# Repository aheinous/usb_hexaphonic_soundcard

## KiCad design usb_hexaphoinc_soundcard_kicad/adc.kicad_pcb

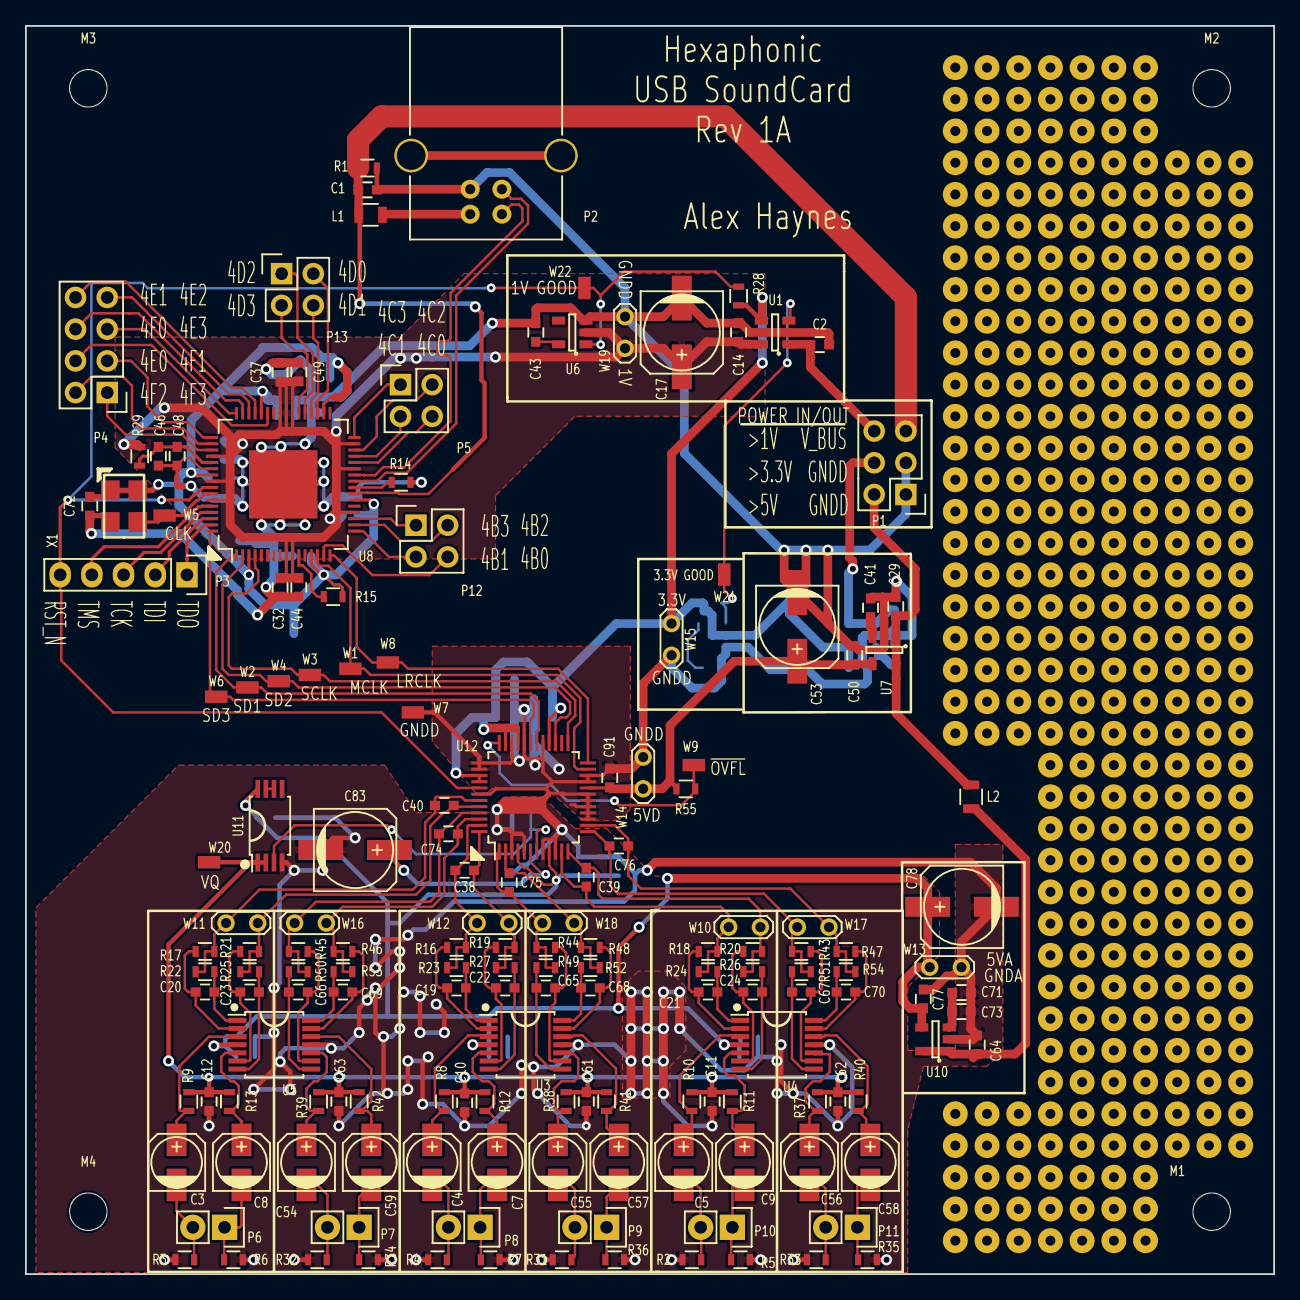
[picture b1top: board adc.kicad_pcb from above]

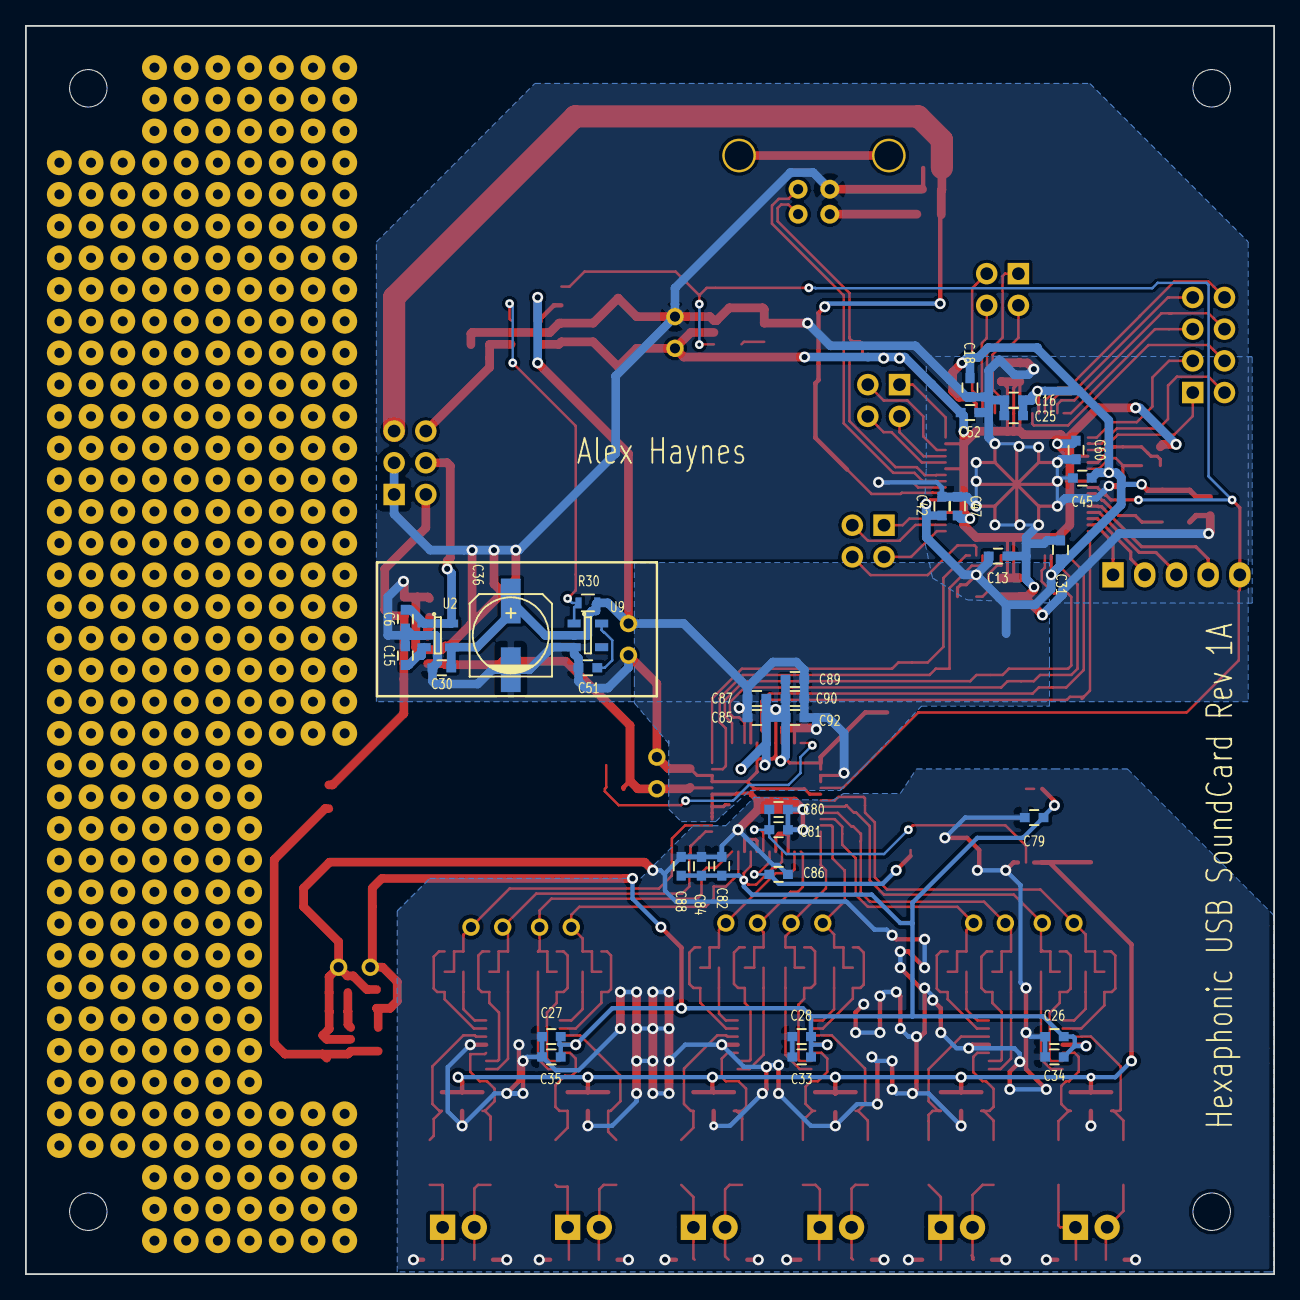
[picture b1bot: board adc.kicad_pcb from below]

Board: 2 copper layers, 100.0 x 100.0 mm, 203 parts (36 on the bottom side), 121 nets.

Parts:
C1, C14: 2.2uF; C_0603
C2, C13, C16, C32, C37, C46, C80, C88, C89: 1uF; C_0603
C3, C4, C5, C7, C8, C9, C54, C55, C56, C57, C58, C59: 10uF; c_elec_4x4.5
C6, C10, C11, C12, C18, C25, C26, C27, C28, C29, C31, C42, C44, C45, C47, C48, C49, C52, C60, C61, C62, C63, C64, C71, C72, C79, C81, C84, C86, C87, C90, C91: 100nF; C_0603
C15, C33, C34, C35, C41, C43, C51, C73, C82, C85, C92: 10nF; C_0603
C17, C36, C53, C78, C83: 220uF; c_elec_6.3x7.7
C19, C20, C21, C22, C23, C24, C65, C66, C67, C68, C69, C70: 470pF; C_0603
C30, C50, C77: 4.7uF; C_0603
C38, C39, C40, C74, C75, C76: 2700pF; C_0603
L1, L2: MPZ2012S102A; R_0805
M1, M2, M3, M4: mounting_hole; MountingHole_3mm
P1: CONN_02X03; Pin_Header_Straight_2x03
P2: USB_B
P3: CONN_01X05; Pin_Header_Straight_1x05
P4: CONN_02X04; Pin_Header_Straight_2x04
P5, P12, P13: CONN_02X02; Pin_Header_Straight_2x02
P6, P7, P8, P9, P10, P11: CONN_01X02; Pin_Header_Straight_1x02
R1, R2, R3, R4, R5, R6, R7, R28, R30, R31, R32, R33, R34, R35, R36, R55: 100k; R_0603
R8, R9, R10, R11, R12, R13, R37, R38, R39, R40, R41, R42: 10k; R_0603
R14: 43.2R 1%; R_0603
R15: 1k; R_0603
R16, R17, R18, R19, R20, R21, R43, R44, R45, R46, R47, R48: 634R; R_0603
R22, R23, R24, R25, R26, R27, R49, R50, R51, R52, R53, R54: 91R; R_0603
R29: 4.7R; R_0603
ST1: star_pt; star_connect_2
ST2: star_pt_2; star_connect_2
U1: NCP4671DSN10T1G; SOT-23-5
U2: NJM2870F33; SOT-23-5
U3, U4, U5: OPA1654; TSSOP-14_4.4x5mm_Pitch0.65mm_better
U6: NCP303; SOT-23-5
U7, U10: NJM2870F05; SOT-23-5
U8: XUF208-128-TQ64; LQFP-64_10x10mm_Pitch0.5mm_center_pad
U9: BD5331G-TR; SOT-23-5
U11: TL072; TSSOP-8_4.4x3mm_Pitch0.65mm_better
U12: CS5366; LQFP-48_7x7mm_Pitch0.5mm_better
W1, W2, W3, W4, W5, W6, W7, W8, W9, W20, W21, W22: TEST_1P; test_point_harwin_S2761-46R
W10, W11, W12, W13, W14, W15, W16, W17, W18, W19: TEST; Test_Point_2Pads
X1: 24MHz; SG5032_crystal_oscillator

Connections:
+3V3: C13.1, C16.1, C18.1, C25.1, C30.1, C31.1, C36.1, C42.1, C45.1, C72.1, C85.1, C87.1, C89.1, C90.1, C92.1, R15.2, R28.1, R30.1, U1.4, U2.4, U8.3, U8.13, U8.22, U8.34, U8.44, U8.55, U9.2, U12.28, U12.33, U12.35, U12.39, U12.40, W15.1, X1.1, X1.4
/Buffer_1_2/ADC_A+: C40.1, R21.1, R25.2, U12.44, W11.2
/Buffer_1_2/ADC_A-: C40.2, R17.1, R22.2, U12.43, W11.1
/Buffer_1_2/ADC_B+: C74.1, R46.1, R53.2, U12.46, W16.2
/Buffer_1_2/ADC_B-: C74.2, R45.1, R50.2, U12.45, W16.1
/Buffer_1_2/IN_A+: C8.2, P6.1, R6.2
/Buffer_1_2/IN_A-: C3.2, P6.2, R3.2
/Buffer_1_2/IN_B+: C59.2, P7.1, R34.2
/Buffer_1_2/IN_B-: C54.2, P7.2, R32.2
/Buffer_1_2/VQ: C10.2, C11.2, C12.2, C61.2, C62.2, C63.2, R8.1, R9.1, R10.1, R11.2, R12.2, R13.2, R37.1, R38.1, R39.1, R40.2, R41.2, R42.2, U11.1, U11.2, W20.1
/Buffer_4_3/ADC_A+: C38.1, R19.1, R27.2, U12.48, W12.2
/Buffer_4_3/ADC_A-: C38.2, R16.1, R23.2, U12.47, W12.1
/Buffer_4_3/ADC_B+: C75.1, R48.1, R52.2, U12.2, W18.2
/Buffer_4_3/ADC_B-: C75.2, R44.1, R49.2, U12.1, W18.1
/Buffer_4_3/IN_A+: C7.2, P8.1, R7.2
/Buffer_4_3/IN_A-: C4.2, P8.2, R4.2
/Buffer_4_3/IN_B+: C57.2, P9.1, R36.2
/Buffer_4_3/IN_B-: C55.2, P9.2, R31.2
/Buffer_6_5/ADC_A+: C39.1, R20.1, R26.2, U12.12, W10.2
/Buffer_6_5/ADC_A-: C39.2, R18.1, R24.2, U12.11, W10.1
/Buffer_6_5/ADC_B+: C76.1, R47.1, R54.2, U12.14, W17.2
/Buffer_6_5/ADC_B-: C76.2, R43.1, R51.2, U12.13, W17.1
/Buffer_6_5/IN_A+: C9.2, P10.1, R5.2
/Buffer_6_5/IN_A-: C5.2, P10.2, R2.2
/Buffer_6_5/IN_B+: C58.2, P11.1, R35.2
/Buffer_6_5/IN_B-: C56.2, P11.2, R33.2
/FILT+: C83.1, C86.1, U12.6
/MCU/4B0: P12.4, U8.15
/MCU/4B1: P12.3, U8.17
/MCU/4B2: P12.2, U8.18
/MCU/4B3: P12.1, U8.19
/MCU/4C0: P5.4, U8.28
/MCU/4C1: P5.3, U8.29
/MCU/4C2: P5.2, U8.30
/MCU/4C3: P5.1, U8.32
/MCU/4D0: P13.2, U8.35
/MCU/4D1: P13.4, U8.36
/MCU/4D2: P13.1, U8.37
/MCU/4D3: P13.3, U8.38
/MCU/4E0: P4.4, U8.43
/MCU/4E1: P4.8, U8.45
/MCU/4E2: P4.7, U8.46
/MCU/4E3: P4.5, U8.48
/MCU/4F0: P4.6, U8.47
/MCU/4F1: P4.3, U8.49
/MCU/4F2: P4.2, U8.50
/MCU/4F3: P4.1, U8.51
/MCU/CLK: U8.58, W5.1, X1.3
/MCU/LRCLK: U8.16, U12.24, W8.1
/MCU/MCLK: U8.14, U12.23, W1.1
/MCU/SCLK: U8.4, U12.25, W3.1
/MCU/SD1: U8.1, U12.30, W2.1
/MCU/SD2: U8.2, U12.27, W4.1
/MCU/SD3: U8.64, U12.31, W6.1
/MCU/USB_D+: P2.3, U8.25
/MCU/USB_D-: P2.2, U8.26
/MCU/V_BUS: C1.1, L1.1, P1.5, R1.2, U8.23
/Power/1V_GOOD: P3.5, R28.2, U6.1, U8.57, U12.41, W22.1
/Power/3.3V_GOOD: R30.2, U1.3, U9.1, W21.1
/Power/GT_1V: C2.1, P1.6, U1.1
/Power/GT_5V: C29.1, L2.1, P1.2, U7.1, U7.5
/Power/GT_33V: C6.1, P1.4, U2.1, U2.5
/VQ: C80.1, C81.1, U11.3, U12.7
Earth_Clean: C46.2, C48.2, ST1.2, U8.54
GNDA: C10.1, C11.1, C12.1, C26.1, C27.1, C28.1, C33.1, C34.1, C35.1, C61.1, C62.1, C63.1, C64.2, C71.2, C73.2, C77.2, C78.2, C79.2, C80.2, C81.2, C82.2, C83.2, C84.2, C86.2, C88.2, R2.1, R3.1, R4.1, R5.1, R6.1, R7.1, R31.1, R32.1, R33.1, R34.1, R35.1, R36.1, ST2.1, U3.11, U4.11, U5.11, U10.2, U11.4, U12.3, U12.5, U12.8, U12.10, W13.2
GNDD: C1.2, C2.2, C6.2, C13.2, C14.2, C15.2, C16.2, C17.2, C18.2, C25.2, C29.2, C30.2, C31.2, C32.2, C36.2, C37.2, C41.2, C42.2, C43.2, C44.2, C45.2, C47.2, C49.2, C50.2, C51.2, C52.2, C53.2, C60.2, C72.2, C85.2, C87.2, C89.2, C90.2, C91.2, C92.2, P1.1, P1.3, P2.4, R1.1, R14.2, ST1.1, ST2.2, U1.2, U2.2, U6.3, U7.2, U8.GND, U9.3, U12.15, U12.16, U12.17, U12.18, U12.19, U12.21, U12.22, U12.29, U12.32, U12.34, U12.37, U12.38, U12.42, W7.1, W14.2, W15.2, W19.2, X1.2
unnamed: C3.1, R9.2, U5.3
unnamed: C4.1, R8.2, U3.3
unnamed: C5.1, R10.2, U4.3
unnamed: C7.1, R12.1, U3.5
unnamed: C8.1, R13.1, U5.5
unnamed: C9.1, R11.1, U4.5
unnamed: C15.1, U2.3
unnamed: C19.1, R23.1, U3.1
unnamed: C19.2, R16.2, U3.2
unnamed: C20.1, R22.1, U5.1
unnamed: C20.2, R17.2, U5.2
unnamed: C21.1, R24.1, U4.1
unnamed: C21.2, R18.2, U4.2
unnamed: C22.1, R27.1, U3.7
unnamed: C22.2, R19.2, U3.6
unnamed: C23.1, R25.1, U5.7
unnamed: C23.2, R21.2, U5.6
unnamed: C24.1, R26.1, U4.7
unnamed: C24.2, R20.2, U4.6
unnamed: C41.1, U7.3
unnamed: C43.1, U6.5
unnamed: C46.1, C48.1, R29.2, U8.53
unnamed: C51.1, U9.5
unnamed: C54.1, R39.2, U5.10
unnamed: C55.1, R38.2, U3.10
unnamed: C56.1, R37.2, U4.10
unnamed: C57.1, R41.1, U3.12
unnamed: C58.1, R40.1, U4.12
unnamed: C59.1, R42.1, U5.12
unnamed: C64.1, L2.2, U10.1, U10.5
unnamed: C65.1, R49.1, U3.8
unnamed: C65.2, R44.2, U3.9
unnamed: C66.1, R50.1, U5.8
unnamed: C66.2, R45.2, U5.9
unnamed: C67.1, R51.1, U4.8
unnamed: C67.2, R43.2, U4.9
unnamed: C68.1, R52.1, U3.14
unnamed: C68.2, R48.2, U3.13
unnamed: C69.1, R53.1, U5.14
unnamed: C69.2, R46.2, U5.13
unnamed: C70.1, R54.1, U4.14
unnamed: C70.2, R47.2, U4.13
unnamed: C71.1, C73.1, U10.3
unnamed: L1.2, P2.1
unnamed: P3.1, U8.63
unnamed: P3.2, U8.62
unnamed: P3.3, U8.61
unnamed: P3.4, U8.60
unnamed: R14.1, U8.24
unnamed: R15.1, U8.11
unnamed: R55.2, U12.36, W9.1
unnamed: U11.6, U11.7
VA: C26.2, C27.2, C28.2, C33.2, C34.2, C35.2, C77.1, C78.1, C79.1, C82.1, C84.1, C88.1, U3.4, U4.4, U5.4, U10.4, U11.8, U12.4, U12.9, W13.1
VDD: C14.1, C17.1, C32.1, C37.1, C44.1, C47.1, C49.1, C52.1, C60.1, R29.1, U1.5, U6.2, U8.9, U8.10, U8.20, U8.27, U8.31, U8.39, U8.40, U8.41, U8.52, U8.56, U8.59, W19.1
VX: C50.1, C53.1, C91.1, R55.1, U7.4, U12.20, W14.1

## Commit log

2016-03-05 Initial Commit.
    Initial design complete but not tested.
2016-03-08 Added media.
    Added PDFs of schematic and PNGs of board.
